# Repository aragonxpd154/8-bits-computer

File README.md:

<h1 align="center">

<br>
</h1>

<h4 align="center">

Computador de 8 bits feito só com lógica TTL (série 74LS), EEPROMs e temporizadores 555 —
**sem microcontrolador, sem CPU pronta**, "como antigamente". Projeto educacional e hobby,
com esquemas, placas (PCB) e manual para fabricar e montar tudo em casa.

</h4>

<p align="center">

</p>

<p align="center">

</p>

<p align="center">
<a href="#-o-que-é">O que é</a> ·
<a href="#-status">Status</a> ·
<a href="#-o-computador-montado">Montado</a> ·
<a href="#-as-placas-em-3d">Placas em 3D</a> ·
<a href="#-passo-a-passo-faça-você-mesmo">Faça você mesmo</a> ·
<a href="#-conteúdo-do-repositório">Conteúdo</a> ·
<a href="#-ferramentas">Ferramentas</a> ·
<a href="#-licença">Licença</a>
</p>

## 🧠 O que é

Um computador completo de 8 bits dividido em **13 módulos** (um deles opcional) + **1 backplane** (placa-mãe de interligação):

| Módulo | Principais CIs | Função |
|---|---|---|
| [Clock](docs/placas/clock-astavel-monoestavel.md) | NE556, 74LS00, 74LS04 | clock automático (0,7–140 Hz) ou passo a passo, HLT |
| [Reset](docs/placas/reset-circuito.md) | 74LS132 | reset por botão e ao ligar |
| [Contador de Programa](docs/placas/pc-contador-programa.md) | 74LS161, 74LS245 | endereço da próxima instrução |
| [RAM e MAR](docs/placas/ram-mar-memoria.md) | 2× 74S189, 74LS173, 4× 74LS157 | 16 bytes, programação manual por chaves DIP |
| [Registrador de Instrução](docs/placas/ir-registrador-instrucao.md) | 2× 74LS173, 74LS245 | opcode + operando |
| [Decodificador de Controle](docs/placas/cd-decodificador-controle.md) | 3× EEPROM 28C16 | microcódigo: 18 sinais de controle |
| [Palavra de Controle](docs/placas/cw-palavra-de-controle.md) *(opcional)* | 3× 74HCT541 | 18 LEDs: mostra os sinais de controle em cada passo |
| [Contador de Passos](docs/placas/fetch-contador-passos.md) | 74LS161, 74LS138 | passos T0…T4 |
| Registrador [A](docs/placas/acc-registrador-a.md) / [B](docs/placas/b-registrador-b.md) | 2× 74LS173 (+ 74LS245) | acumulador e segundo operando |
| [ULA](docs/placas/alu-unidade-logica-aritmetica.md) | 74LS283, 74LS86, 74LS08, 74LS32, 74LS153 | soma, subtração, AND, OR, XOR, NOT |
| [Registrador de Saída](docs/placas/out-registrador-saida.md) | 2× 74LS173 | valor do display |
| [Display Decimal](docs/placas/display-decimal.md) | 28C16, 555, 74LS161, 74LS139 | 0…255 ou −128…127 em 4 dígitos |
| [Backplane](docs/placas/backplane-barramento.md) |  | 5 V protegido, barramento D0…D7 com LEDs, todos os sinais |

**16 instruções:** `NOP LDA LDI STA ADD SUB AND OR XOR NOT JMP JC JZ OUT HLT` (JC/JZ prontos para uma futura placa de flags).
Detalhes em [docs/01-arquitetura.md](docs/01-arquitetura.md). Clique no nome de um módulo para ver a página dele.

## 🧱 O computador montado

As 14 placas numa base de madeira de 65 × 56 cm, em espaçadores de 25 mm, com tampa de acrílico. Os 58 cabos
passam por baixo das placas, presos com enforca-gatos. Na versão 3D os LEDs e o display funcionam de verdade:
a página roda o mesmo microcódigo das EEPROMs (Fibonacci, contador, tabuada…), com clock ajustável e passo a passo.

<p align="center"></p>

Arranjo, medidas e comprimento de cada cabo: [docs/05-interligacao-e-backplane.md](docs/05-interligacao-e-backplane.md).

## 🧊 As placas em 3D

Cada placa tem uma **página própria** explicando a função dela no computador, como o circuito funciona, o papel
de cada CI, o que cada LED mostra, o esquemático, a pinagem dos conectores, a lista de componentes e como testar —
além do **modelo 3D** (STL que o GitHub mostra girando no navegador, GLB com as cores reais e STEP para CAD).

<p align="center"></p>

➡️ **[Guia das 13 placas](docs/placas/README.md)** · 🧊 **[3D Viewer (GitHub Pages)](https://aragonxpd154.github.io/8-bits-computer/docs/3d/visualizador.html)** · [como usar e arquivos 3D](docs/3d/README.md)

<table>
<tr>
<td align="center" width="33%"><a href="docs/placas/ram-mar-memoria.md"><br><b>RAM e MAR</b></a></td>
<td align="center" width="33%"><a href="docs/placas/alu-unidade-logica-aritmetica.md"><br><b>ULA</b></a></td>
<td align="center" width="33%"><a href="docs/placas/display-decimal.md"><br><b>Display Decimal</b></a></td>
</tr>
<tr>
<td align="center"><a href="docs/placas/clock-astavel-monoestavel.md"><br><b>Clock</b></a></td>
<td align="center"><a href="docs/placas/cd-decodificador-controle.md"><br><b>Decodificador de Controle</b></a></td>
<td align="center"><a href="docs/placas/backplane-barramento.md"><br><b>Backplane</b></a></td>
</tr>
</table>

## 💻 Status

**Versão 3.0 (novembro/2026)**  projeto completo em **KiCad** (abre no Zorin OS/Ubuntu/Windows):

- [x] Esquemáticos de todos os módulos, com bloco de título e autoria
- [x] PCBs roteadas de todas as 14 placas, **DRC sem erros**  prontas para fabricação profissional (JLCPCB/PCBWay) e com **serigrafia didática** (sinais nos conectores e LEDs, valores dos componentes)
- [x] PDFs 1:1 para transferência térmica, fotolitos, mapa de furação e Gerbers para fabricação industrial
- [x] Backplane (antiga pasta *ASSEMBLY LAYOUT*, que estava vazia) e placa de Reset (que não tinha PCB)
- [x] Microcódigo completo (Python e C), EEPROM do display, montador e emulador
- [x] Teste automático do microcódigo: 14 programas de teste, um para cada instrução (`firmware/ferramentas/testar.py`)
- [x] Revisão de todos os circuitos  9 erros corrigidos (veja [docs/02-revisao-e-correcoes.md](docs/02-revisao-e-correcoes.md))
- [x] Manual completo de fabricação, montagem, gravação e uso
- [x] Página detalhada de cada placa, com diagrama de funcionamento e **modelo 3D** (STL, GLB, STEP e visualizador)
- [ ] Testes em bancada de cada placa produzida (o Clock da versão 2.1 já foi testado)
- [ ] Placa de flags (carry/zero) para `JC`/`JZ`

## ☕ Passo a passo (faça você mesmo)

> 🖼️ **Comece pelo [Guia visual passo a passo](docs/GUIA-VISUAL-PASSO-A-PASSO.md)**  todo o caminho em diagramas,
> do arquivo ao computador funcionando. Também em PDF:
> 📕 [Guia visual (PDF)](docs/pdf/guia-visual-passo-a-passo.pdf) · 📘 [Manual completo (PDF)](docs/pdf/manual-completo.pdf) ·
> 📄 [Esquema elétrico completo (PDF)](hardware/esquema-eletrico-completo.pdf)

Manual detalhado, capítulo por capítulo  tudo em português:

1. [Arquitetura](docs/01-arquitetura.md)  entenda o computador
2. [Revisão e correções](docs/02-revisao-e-correcoes.md)  o que mudou desde a versão EasyEDA
3. [Fabricação das placas](docs/03-fabricacao-das-placas.md)  enviar os Gerbers para a China (JLCPCB/PCBWay)
4. [Montagem das placas](docs/04-montagem-das-placas.md)  componente por componente, com testes
5. [Interligação e backplane](docs/05-interligacao-e-backplane.md)  os 58 cabos e o arranjo na base
6. [Gravação das EEPROMs](docs/06-gravacao-das-eeproms.md)  microcódigo e display com `minipro`
7. [Programação e uso](docs/07-programacao-e-uso.md)  escrever, montar e rodar programas
8. [Testes e diagnóstico](docs/08-testes-e-diagnostico.md)

📄 **Esquema elétrico completo em um único PDF:** [hardware/esquema-eletrico-completo.pdf](hardware/esquema-eletrico-completo.pdf)
🧾 **Lista de materiais:** [docs/lista-de-materiais-completa.md](docs/lista-de-materiais-completa.md)
🧊 **Cada placa explicada, em 3D:** [docs/placas/README.md](docs/placas/README.md)
🛠️ **Placas (imagens, tamanhos, arquivos):** [hardware/README.md](hardware/README.md)

## 📁 Conteúdo do repositório

```
8-bits-computer/
├── README.md                     este arquivo (visão geral, passo a passo, conteúdo)
├── CHANGELOG.md                  histórico de versões
├── LICENSE                       GPL-3.0
├── docs/                         MANUAL COMPLETO (pt-BR)
│   ├── GUIA-VISUAL-PASSO-A-PASSO.md  o projeto inteiro em diagramas, etapa por etapa
│   ├── placas/                       UMA PÁGINA POR PLACA: função, funcionamento, 3D, esquema, conectores, teste
│   ├── 3d/                           visualizador das placas, computador montado (montagem.html), modelos .glb/.stl
│   ├── pdf/                          guia visual e manual completo em PDF
│   ├── 01-arquitetura.md             blocos, instruções, tabela de todos os sinais
│   ├── 02-revisao-e-correcoes.md     erros corrigidos em relação à versão EasyEDA
│   ├── 03-fabricacao-das-placas.md   como pedir as PCBs no JLCPCB/PCBWay
│   ├── 04-montagem-das-placas.md     soldagem e teste de cada placa
│   ├── 05-interligacao-e-backplane.md os 58 cabos e o arranjo na base
│   ├── 06-gravacao-das-eeproms.md    gravação com minipro (Zorin/Ubuntu)
│   ├── 07-programacao-e-uso.md       painel, montador, emulador, exemplos
│   ├── 08-testes-e-diagnostico.md    subida do sistema e problemas comuns
│   ├── lista-de-materiais-completa.md
│   └── imagens/                      diagramas, imagens 2D/3D das placas, esquemas e diagramas de funcionamento
├── hardware/
│   ├── README.md                     tabela das 14 placas (tamanho, imagens, links)
│   ├── esquema-eletrico-completo.pdf capa + diagrama + interligação + 13 esquemáticos
│   ├── kicad/<placa>/                projeto KiCad (.kicad_pro / .kicad_sch / .kicad_pcb)
│   ├── kicad/bibliotecas/            símbolos e footprints do projeto
│   └── fabricacao/<placa>/           <placa>-gerber.zip (vai para a fábrica), esquemático PDF,
│                                     guia de montagem 1:1, mapa de furação, BOM, DRC, modelo 3D .step
├── firmware/
│   ├── microcodigo/                  EEPROM0/1/2.bin + gerador (Python e C)
│   ├── display/                      DISPLAY.bin + gerador
│   ├── programas/                    6 exemplos + 14 programas de teste (testes/)
│   └── ferramentas/                  montador.py, emulador.py e testar.py
└── tools/                            geradores: hardware (KiCad), 3D, documentação, diagramas, PDFs
```

### As 14 placas

| # | Placa (clique para a página) | Pasta |
|---|---|---|
| 1 | [Backplane / Barramento](docs/placas/backplane-barramento.md) | `backplane-barramento` |
| 2 | [Clock](docs/placas/clock-astavel-monoestavel.md) | `clock-astavel-monoestavel` |
| 3 | [Reset](docs/placas/reset-circuito.md) | `reset-circuito` |
| 4 | [Contador de Programa](docs/placas/pc-contador-programa.md) | `pc-contador-programa` |
| 5 | [RAM e MAR](docs/placas/ram-mar-memoria.md) | `ram-mar-memoria` |
| 6 | [Registrador de Instrução](docs/placas/ir-registrador-instrucao.md) | `ir-registrador-instrucao` |
| 7 | [Decodificador de Controle](docs/placas/cd-decodificador-controle.md) | `cd-decodificador-controle` |
| 8 | [Palavra de Controle](docs/placas/cw-palavra-de-controle.md) *(opcional)* | `cw-palavra-de-controle` |
| 9 | [Contador de Passos](docs/placas/fetch-contador-passos.md) | `fetch-contador-passos` |
| 10 | [Registrador A](docs/placas/acc-registrador-a.md) | `acc-registrador-a` |
| 11 | [Registrador B](docs/placas/b-registrador-b.md) | `b-registrador-b` |
| 12 | [ULA](docs/placas/alu-unidade-logica-aritmetica.md) | `alu-unidade-logica-aritmetica` |
| 13 | [Registrador de Saída](docs/placas/out-registrador-saida.md) | `out-registrador-saida` |
| 14 | [Display Decimal](docs/placas/display-decimal.md) | `display-decimal` |

> As versões antigas em EasyEDA (1.0V–3.0V, 2021) ficam preservadas no histórico do Git, na tag
> [`v2-easyeda`](https://github.com/aragonxpd154/8-bits-computer/tree/v2-easyeda).

## 🚀 Ferramentas

- [KiCad](https://www.kicad.org/) 7 ou superior  esquemáticos e PCBs
- [Freerouting](https://github.com/freerouting/freerouting)  autorroteamento
- [three.js](https://threejs.org/), trimesh e cascadio  modelos e visualizador 3D
- Python 3  microcódigo, montador, emulador e geradores
- `minipro` + TL866II Plus/T48  gravação das EEPROMs
- Histórico: EasyEDA, LTspice, MultisimLive, Hexplorer, Code::Blocks

Para regerar todo o hardware a partir da descrição em Python, veja [tools/gerador-kicad/README.md](tools/gerador-kicad/README.md).

## 📝 Licença

Este projeto está sob a licença GPL v3.0. Veja o arquivo [LICENSE](LICENSE).

---

Projeto e autoria: **Marcos Silva dos Santos (MarcosObel)** ♥  [LinkedIn](https://www.linkedin.com/in/marcosobel) · [GitHub](https://github.com/aragonxpd154)

<sub>English summary: an 8-bit TTL computer (SAP-1 style, no microcontroller) by Marcos Silva dos Santos. Version 3.0 contains complete KiCad schematics and home-fabrication-friendly PCBs for all 13 boards, corrected microcode, EEPROM images, an assembler/emulator, a page per board with 3D models (STL/GLB/STEP and an interactive viewer), and a full build manual (in Portuguese) under `docs/`.</sub>

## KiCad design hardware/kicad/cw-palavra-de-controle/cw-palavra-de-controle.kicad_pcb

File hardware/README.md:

# Hardware — Computador 8 Bits v3.0

> Projeto e PCBs de **Marcos Silva dos Santos** (MarcosObel) — GPL-3.0. Gerado por `tools/gerar_docs.py`.

- `kicad/<placa>/` — projeto KiCad (abra o `.kicad_pro`). Formato KiCad 7 (abre no 7, 8 e 9).
- `fabricacao/<placa>/` — **Gerber para a fábrica**, guia de montagem 1:1, esquemático, BOM, relatório DRC.
- [`esquema-eletrico-completo.pdf`](esquema-eletrico-completo.pdf) — todos os esquemáticos num único PDF.
- `fabricacao/<placa>/<placa>.step` — modelo 3D mecânico; modelos para visualizar em [`docs/3d/`](../docs/3d/README.md).
- **Explicação detalhada de cada placa:** [docs/placas](../docs/placas/README.md).

Todas: 2 camadas, furo metalizado, trilha 0,5 mm (alimentação 0,9 mm), isolação 0,4 mm, vias 1,6/0,8 mm, 4 furos M3 nos cantos, serigrafia didática. Como pedir: [docs/03-fabricacao-das-placas.md](../docs/03-fabricacao-das-placas.md).

| Placa | Tamanho (mm) | Vias | Trilhas na face de cima | Esquema | Fabricação |
|---|---|---:|---:|---|---|
| **Clock Astavel / Monoestavel** | 105 × 86 | 4 | 96 segmentos | [PDF](fabricacao/clock-astavel-monoestavel/0-esquematico.pdf) | [arquivos](fabricacao/clock-astavel-monoestavel/) |
| **Circuito de Reset** | 67 × 58 | 0 | 33 segmentos | [PDF](fabricacao/reset-circuito/0-esquematico.pdf) | [arquivos](fabricacao/reset-circuito/) |
| **Contador de Programa (PC)** | 92 × 69 | 5 | 93 segmentos | [PDF](fabricacao/pc-contador-programa/0-esquematico.pdf) | [arquivos](fabricacao/pc-contador-programa/) |
| **Memoria RAM e MAR** | 145 × 139 | 151 | 866 segmentos | [PDF](fabricacao/ram-mar-memoria/0-esquematico.pdf) | [arquivos](fabricacao/ram-mar-memoria/) |
| **Registrador de Instrucao (IR)** | 102 × 69 | 6 | 125 segmentos | [PDF](fabricacao/ir-registrador-instrucao/0-esquematico.pdf) | [arquivos](fabricacao/ir-registrador-instrucao/) |
| **Decodificador de Controle (microcodigo)** | 161 × 61 | 6 | 144 segmentos | [PDF](fabricacao/cd-decodificador-controle/0-esquematico.pdf) | [arquivos](fabricacao/cd-decodificador-controle/) |
| **Palavra de Controle (18 LEDs)** | 145 × 82 | 25 | 289 segmentos | [PDF](fabricacao/cw-palavra-de-controle/0-esquematico.pdf) | [arquivos](fabricacao/cw-palavra-de-controle/) |
| **Contador de Passos (Fetch/Execute)** | 70 × 69 | 2 | 86 segmentos | [PDF](fabricacao/fetch-contador-passos/0-esquematico.pdf) | [arquivos](fabricacao/fetch-contador-passos/) |
| **Registrador A (Acumulador)** | 110 × 69 | 4 | 174 segmentos | [PDF](fabricacao/acc-registrador-a/0-esquematico.pdf) | [arquivos](fabricacao/acc-registrador-a/) |
| **Registrador B** | 110 × 69 | 8 | 160 segmentos | [PDF](fabricacao/b-registrador-b/0-esquematico.pdf) | [arquivos](fabricacao/b-registrador-b/) |
| **Unidade Logica e Aritmetica (ULA)** | 218 × 128 | 145 | 837 segmentos | [PDF](fabricacao/alu-unidade-logica-aritmetica/0-esquematico.pdf) | [arquivos](fabricacao/alu-unidade-logica-aritmetica/) |
| **Registrador de Saida (OUT)** | 110 × 69 | 0 | 95 segmentos | [PDF](fabricacao/out-registrador-saida/0-esquematico.pdf) | [arquivos](fabricacao/out-registrador-saida/) |
| **Display Decimal** | 134 × 112 | 11 | 174 segmentos | [PDF](fabricacao/display-decimal/0-esquematico.pdf) | [arquivos](fabricacao/display-decimal/) |
| **Backplane / Barramento (Assembly Layout)** | 204 × 153 | 14 | 202 segmentos | [PDF](fabricacao/backplane-barramento/0-esquematico.pdf) | [arquivos](fabricacao/backplane-barramento/) |

Vermelho = cobre da face de cima (componentes) · azul = cobre da face de baixo (solda) · amarelo = serigrafia.

## Clock Astavel / Monoestavel

NE556: metade astavel (clock automatico ajustavel) e metade monoestavel (passo manual sem repique). Chave AUTO/MANUAL, entrada HLT.

🧊 **[Página completa da placa](../docs/placas/clock-astavel-monoestavel.md)** (função, funcionamento, esquema, conectores, teste) · [3D (STL)](../docs/3d/stl/clock-astavel-monoestavel.stl) · [STEP](fabricacao/clock-astavel-monoestavel/clock-astavel-monoestavel.step)

| Em 3D | Cobre e serigrafia |
|---|---|
|  |  |

## Circuito de Reset

Gera RST e ~{RST} (botao + reset automatico ao ligar) e o ~{STEPCLR} do contador de passos (= ~{RST} AND ~{Y5}).

🧊 **[Página completa da placa](../docs/placas/reset-circuito.md)** (função, funcionamento, esquema, conectores, teste) · [3D (STL)](../docs/3d/stl/reset-circuito.stl) · [STEP](fabricacao/reset-circuito/reset-circuito.step)

| Em 3D | Cobre e serigrafia |
|---|---|
|  |  |

## Contador de Programa (PC)

Contador de 4 bits (74LS161) com carga (JMP) e saida para o barramento (74LS245).

🧊 **[Página completa da placa](../docs/placas/pc-contador-programa.md)** (função, funcionamento, esquema, conectores, teste) · [3D (STL)](../docs/3d/stl/pc-contador-programa.stl) · [STEP](fabricacao/pc-contador-programa/pc-contador-programa.step)

| Em 3D | Cobre e serigrafia |
|---|---|
|  |  |

## Memoria RAM e MAR

MAR (74LS173), RAM 16x8 (2x 74S189), multiplexadores PROG/RUN (74LS157), gravacao manual por chaves DIP e pulso de escrita sincronizado ao clock.

🧊 **[Página completa da placa](../docs/placas/ram-mar-memoria.md)** (função, funcionamento, esquema, conectores, teste) · [3D (STL)](../docs/3d/stl/ram-mar-memoria.stl) · [STEP](fabricacao/ram-mar-memoria/ram-mar-memoria.step)

| Em 3D | Cobre e serigrafia |
|---|---|
|  |  |

## Registrador de Instrucao (IR)

Guarda a instrucao: nibble alto = opcode (para o decodificador), nibble baixo = operando (volta ao barramento por ~{IRO}).

🧊 **[Página completa da placa](../docs/placas/ir-registrador-instrucao.md)** (função, funcionamento, esquema, conectores, teste) · [3D (STL)](../docs/3d/stl/ir-registrador-instrucao.stl) · [STEP](fabricacao/ir-registrador-instrucao/ir-registrador-instrucao.step)

| Em 3D | Cobre e serigrafia |
|---|---|
|  |  |

## Decodificador de Controle (microcodigo)

3 EEPROMs 28C16 com o microcodigo: endereco = FLAGS(A8:A7) OPCODE(A6:A3) PASSO(A2:A0).

🧊 **[Página completa da placa](../docs/placas/cd-decodificador-controle.md)** (função, funcionamento, esquema, conectores, teste) · [3D (STL)](../docs/3d/stl/cd-decodificador-controle.stl) · [STEP](fabricacao/cd-decodificador-controle/cd-decodificador-controle.step)

| Em 3D | Cobre e serigrafia |
|---|---|
|  |  |

## Palavra de Controle (18 LEDs)

Fica entre o Decodificador de Controle e o backplane (que nao muda): recebe os 5 V do conector P_CD e repassa ao Decodificador por J12. 3x 74HCT541 repetem os 20 sinais das EEPROMs (reforcam a saida das EEPROMs) e 18 LEDs mostram cada sinal de controle: LED aceso = sinal ATIVO, inclusive nos sinais com barra (ativos em 0). Opcional: sem ela, os cabos do Decodificador vao direto ao backplane.

🧊 **[Página completa da placa](../docs/placas/cw-palavra-de-controle.md)** (função, funcionamento, esquema, conectores, teste) · [3D (STL)](../docs/3d/stl/cw-palavra-de-controle.stl) · [STEP](fabricacao/cw-palavra-de-controle/cw-palavra-de-controle.step)

| Em 3D | Cobre e serigrafia |
|---|---|
|  |  |

## Contador de Passos (Fetch/Execute)

Contador de passos T0..T4 (74LS161 + 74LS138). ~{Y5} reinicia o contador via placa de Reset.

🧊 **[Página completa da placa](../docs/placas/fetch-contador-passos.md)** (função, funcionamento, esquema, conectores, teste) · [3D (STL)](../docs/3d/stl/fetch-contador-passos.stl) · [STEP](fabricacao/fetch-contador-passos/fetch-contador-passos.step)

| Em 3D | Cobre e serigrafia |
|---|---|
|  |  |

## Registrador A (Acumulador)

Registrador A de 8 bits (2x 74LS173) com saida para o barramento (74LS245) e saida permanente para a ULA.

🧊 **[Página completa da placa](../docs/placas/acc-registrador-a.md)** (função, funcionamento, esquema, conectores, teste) · [3D (STL)](../docs/3d/stl/acc-registrador-a.stl) · [STEP](fabricacao/acc-registrador-a/acc-registrador-a.step)

| Em 3D | Cobre e serigrafia |
|---|---|
|  |  |

## Registrador B

Registrador B de 8 bits; alimenta a entrada B da ULA.

🧊 **[Página completa da placa](../docs/placas/b-registrador-b.md)** (função, funcionamento, esquema, conectores, teste) · [3D (STL)](../docs/3d/stl/b-registrador-b.stl) · [STEP](fabricacao/b-registrador-b/b-registrador-b.step)

| Em 3D | Cobre e serigrafia |
|---|---|
|  |  |

## Unidade Logica e Aritmetica (ULA)

Soma/subtracao (2x 74LS283 + 74LS86), AND, OR, XOR e NOT, selecionados por AL1:AL0 em 4x 74LS153.

🧊 **[Página completa da placa](../docs/placas/alu-unidade-logica-aritmetica.md)** (função, funcionamento, esquema, conectores, teste) · [3D (STL)](../docs/3d/stl/alu-unidade-logica-aritmetica.stl) · [STEP](fabricacao/alu-unidade-logica-aritmetica/alu-unidade-logica-aritmetica.step)

| Em 3D | Cobre e serigrafia |
|---|---|
|  |  |

## Registrador de Saida (OUT)

Registrador de saida: guarda o valor exibido pelo display decimal.

🧊 **[Página completa da placa](../docs/placas/out-registrador-saida.md)** (função, funcionamento, esquema, conectores, teste) · [3D (STL)](../docs/3d/stl/out-registrador-saida.stl) · [STEP](fabricacao/out-registrador-saida/out-registrador-saida.step)

| Em 3D | Cobre e serigrafia |
|---|---|
|  |  |

## Display Decimal

Converte o valor de 8 bits do registrador OUT em decimal (0..255 ou -128..127) por EEPROM 28C16 e varredura de 4 digitos (555 + 74LS161 + 74LS139).

🧊 **[Página completa da placa](../docs/placas/display-decimal.md)** (função, funcionamento, esquema, conectores, teste) · [3D (STL)](../docs/3d/stl/display-decimal.stl) · [STEP](fabricacao/display-decimal/display-decimal.step)

| Em 3D | Cobre e serigrafia |
|---|---|
|  |  |

## Backplane / Barramento (Assembly Layout)

Placa-mae de interligacao: entrada de 5 V protegida, distribuicao de alimentacao, barramento de dados D0..D7 com LEDs, e roteamento de todos os sinais de controle entre os modulos. Cada conector tem a mesma pinagem do conector correspondente no modulo: use cabos de 4 vias RETOS (pino 1 com pino 1).

🧊 **[Página completa da placa](../docs/placas/backplane-barramento.md)** (função, funcionamento, esquema, conectores, teste) · [3D (STL)](../docs/3d/stl/backplane-barramento.stl) · [STEP](fabricacao/backplane-barramento/backplane-barramento.step)

| Em 3D | Cobre e serigrafia |
|---|---|
|  |  |

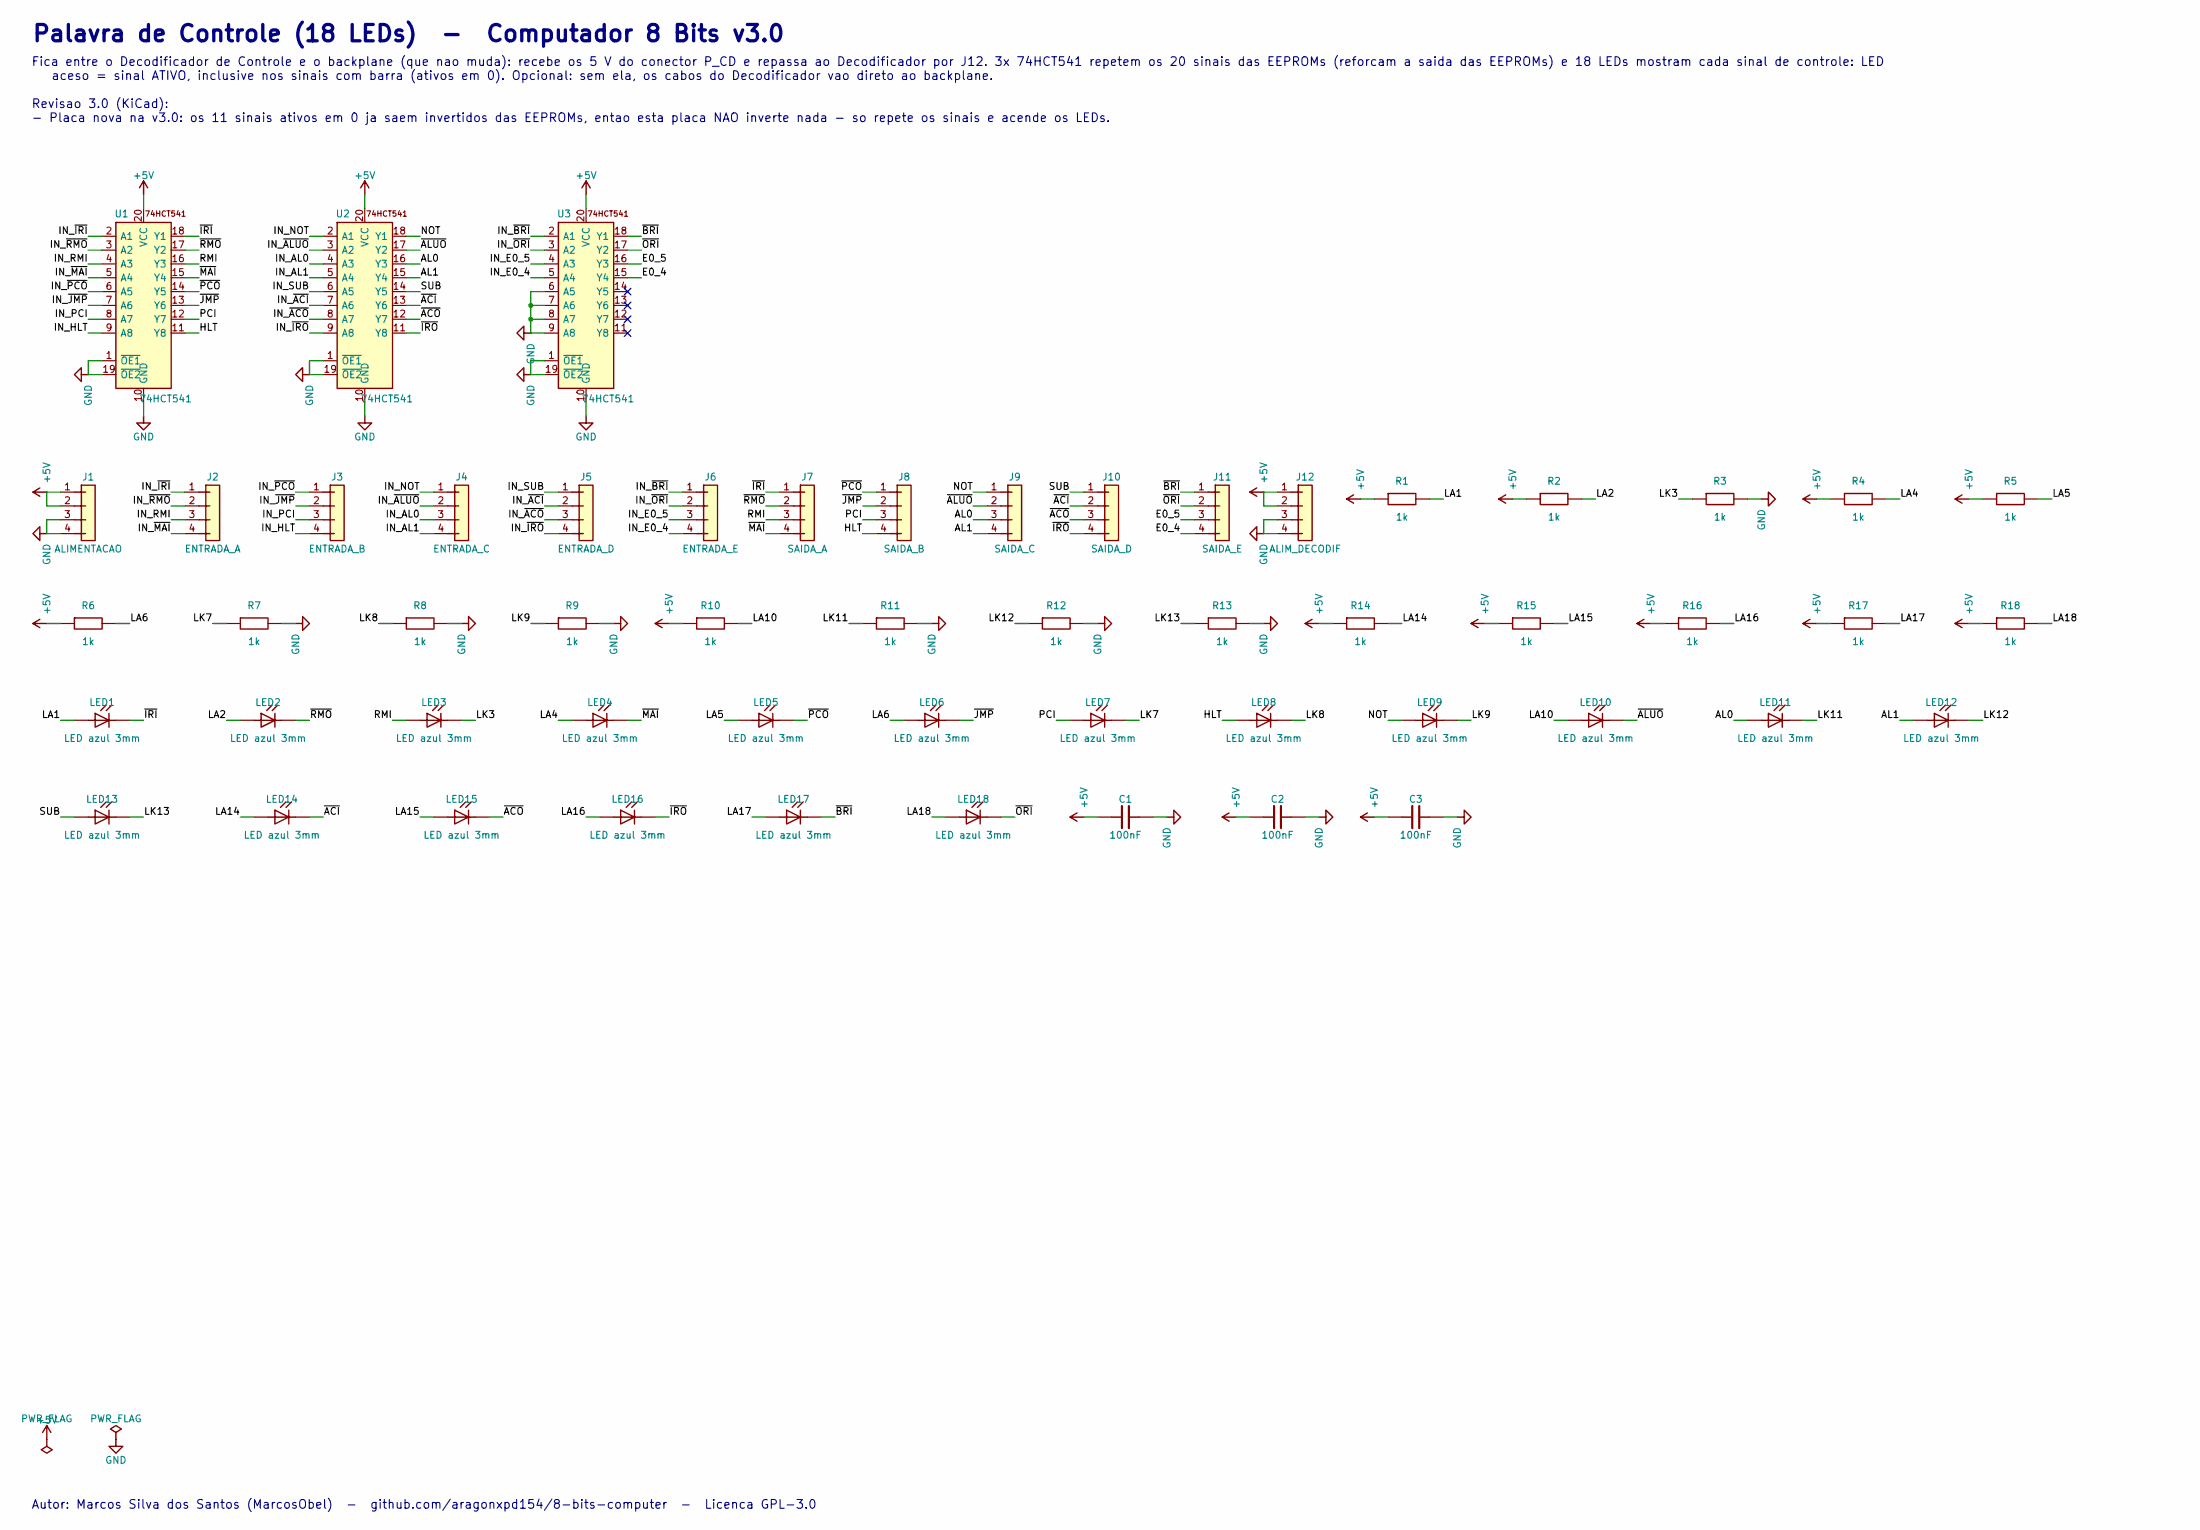
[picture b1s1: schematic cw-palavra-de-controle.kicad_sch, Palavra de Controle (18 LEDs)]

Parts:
C1, C2, C3: 100nF; C_Disc_D5.0mm_W2.5mm_P5.00mm
J1: ALIMENTACAO; PinHeader_1x04_P2.54mm_Vertical
J2: ENTRADA_A; PinHeader_1x04_P2.54mm_Vertical
J3: ENTRADA_B; PinHeader_1x04_P2.54mm_Vertical
J4: ENTRADA_C; PinHeader_1x04_P2.54mm_Vertical
J5: ENTRADA_D; PinHeader_1x04_P2.54mm_Vertical
J6: ENTRADA_E; PinHeader_1x04_P2.54mm_Vertical
J7: SAIDA_A; PinHeader_1x04_P2.54mm_Vertical
J8: SAIDA_B; PinHeader_1x04_P2.54mm_Vertical
J9: SAIDA_C; PinHeader_1x04_P2.54mm_Vertical
J10: SAIDA_D; PinHeader_1x04_P2.54mm_Vertical
J11: SAIDA_E; PinHeader_1x04_P2.54mm_Vertical
J12: ALIM_DECODIF; PinHeader_1x04_P2.54mm_Vertical
LED1, LED2, LED3, LED4, LED5, LED6, LED7, LED8, LED9, LED10, LED11, LED12, LED13, LED14, LED15, LED16, LED17, LED18: LED azul 3mm; LED_D3.0mm
R1, R2, R3, R4, R5, R6, R7, R8, R9, R10, R11, R12, R13, R14, R15, R16, R17, R18: 1k; R_Axial_DIN0207_L6.3mm_D2.5mm_P10.16mm_Horizontal
U1, U2, U3: 74HCT541; DIP-20_W7.62mm_LongPads

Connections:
+5V: C1.1, C2.1, C3.1, J1.1, J1.2, J12.1, J12.2, R1.1, R2.1, R4.1, R5.1, R6.1, R10.1, R14.1, R15.1, R16.1, R17.1, R18.1, U1.20 (VCC), U2.20 (VCC), U3.20 (VCC)
AL0: J9.3, LED11.2 (A), U2.16 (Y3)
AL1: J9.4, LED12.2 (A), U2.15 (Y4)
E0_4: J11.4, U3.15 (Y4)
E0_5: J11.3, U3.16 (Y3)
GND: C1.2, C2.2, C3.2, J1.3, J1.4, J12.3, J12.4, R3.2, R7.2, R8.2, R9.2, R11.2, R12.2, R13.2, U1.1 (~OE1), U1.10 (GND), U1.19 (~OE2), U2.1 (~OE1), U2.10 (GND), U2.19 (~OE2), U3.1 (~OE1), U3.6 (A5), U3.7 (A6), U3.8 (A7), U3.9 (A8), U3.10 (GND), U3.19 (~OE2)
HLT: J8.4, LED8.2 (A), U1.11 (Y8)
IN_AL0: J4.3, U2.4 (A3)
IN_AL1: J4.4, U2.5 (A4)
IN_E0_4: J6.4, U3.5 (A4)
IN_E0_5: J6.3, U3.4 (A3)
IN_HLT: J3.4, U1.9 (A8)
IN_NOT: J4.1, U2.2 (A1)
IN_PCI: J3.3, U1.8 (A7)
IN_RMI: J2.3, U1.4 (A3)
IN_SUB: J5.1, U2.6 (A5)
IN_~ACI: J5.2, U2.7 (A6)
IN_~ACO: J5.3, U2.8 (A7)
IN_~ALUO: J4.2, U2.3 (A2)
IN_~BRI: J6.1, U3.2 (A1)
IN_~IRI: J2.1, U1.2 (A1)
IN_~IRO: J5.4, U2.9 (A8)
IN_~JMP: J3.2, U1.7 (A6)
IN_~MAI: J2.4, U1.5 (A4)
IN_~ORI: J6.2, U3.3 (A2)
IN_~PCO: J3.1, U1.6 (A5)
IN_~RMO: J2.2, U1.3 (A2)
LA1: LED1.2 (A), R1.2
LA2: LED2.2 (A), R2.2
LA4: LED4.2 (A), R4.2
LA5: LED5.2 (A), R5.2
LA6: LED6.2 (A), R6.2
LA10: LED10.2 (A), R10.2
LA14: LED14.2 (A), R14.2
LA15: LED15.2 (A), R15.2
LA16: LED16.2 (A), R16.2
LA17: LED17.2 (A), R17.2
LA18: LED18.2 (A), R18.2
LK3: LED3.1 (K), R3.1
LK7: LED7.1 (K), R7.1
LK8: LED8.1 (K), R8.1
LK9: LED9.1 (K), R9.1
LK11: LED11.1 (K), R11.1
LK12: LED12.1 (K), R12.1
LK13: LED13.1 (K), R13.1
NOT: J9.1, LED9.2 (A), U2.18 (Y1)
PCI: J8.3, LED7.2 (A), U1.12 (Y7)
RMI: J7.3, LED3.2 (A), U1.16 (Y3)
SUB: J10.1, LED13.2 (A), U2.14 (Y5)
~ACI: J10.2, LED14.1 (K), U2.13 (Y6)
~ACO: J10.3, LED15.1 (K), U2.12 (Y7)
~ALUO: J9.2, LED10.1 (K), U2.17 (Y2)
~BRI: J11.1, LED17.1 (K), U3.18 (Y1)
~IRI: J7.1, LED1.1 (K), U1.18 (Y1)
~IRO: J10.4, LED16.1 (K), U2.11 (Y8)
~JMP: J8.2, LED6.1 (K), U1.13 (Y6)
~MAI: J7.4, LED4.1 (K), U1.15 (Y4)
~ORI: J11.2, LED18.1 (K), U3.17 (Y2)
~PCO: J8.1, LED5.1 (K), U1.14 (Y5)
~RMO: J7.2, LED2.1 (K), U1.17 (Y2)

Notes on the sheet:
Palavra de Controle (18 LEDs) - Computador 8 Bits v3.0
Fica entre o Decodificador de Controle e o backplane (que nao muda): recebe os 5 V do conector P_CD e repassa ao Decodificador por J12. 3x 74HCT541 repetem os 20 sinais das EEPROMs (reforcam a saida das EEPROMs) e 18 LEDs mostram cada sinal de controle: LED aceso = sinal ATIVO, inclusive nos sinais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
Autor: Marcos Silva dos Santos (MarcosObel) - github.com/aragonxpd154/8-bits-computer - Licenca GPL-3.0

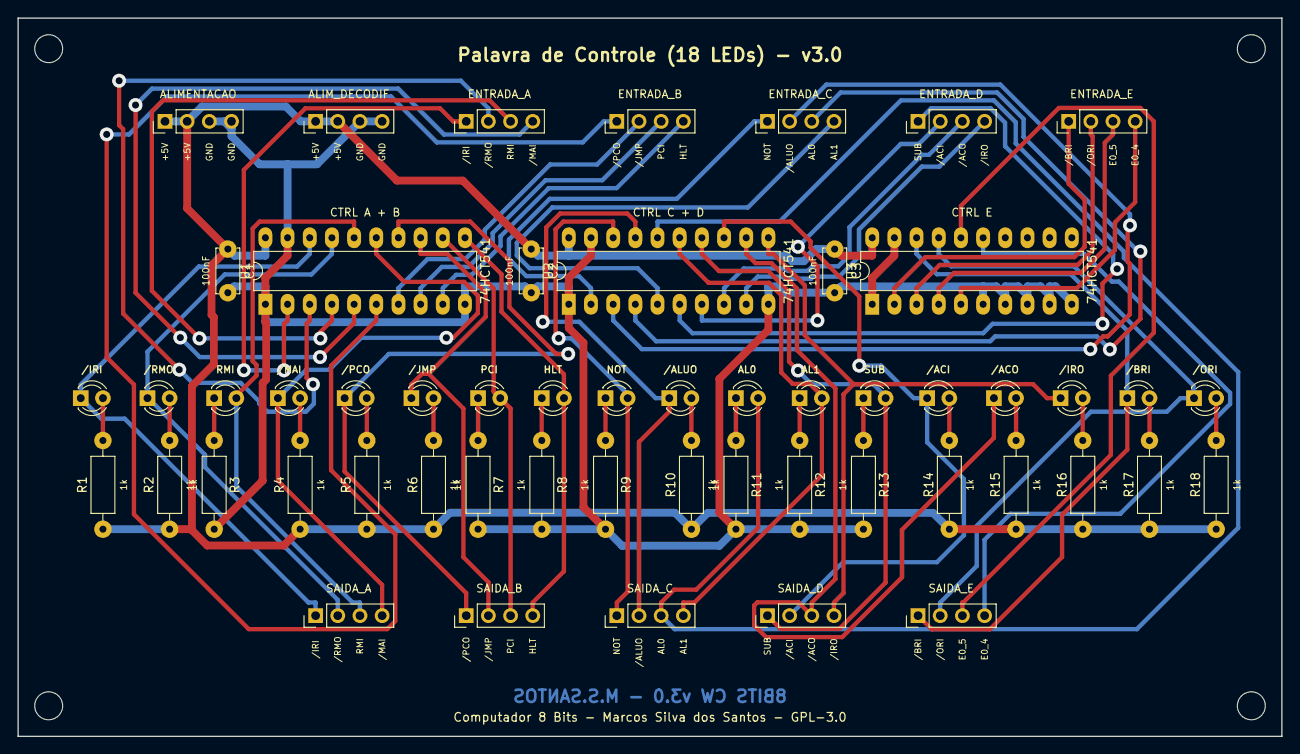
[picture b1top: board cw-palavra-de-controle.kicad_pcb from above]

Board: 2 copper layers, 144.7 x 82.3 mm, 58 parts (0 on the bottom side), 60 nets.

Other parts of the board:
H1, H2, H3, H4: MountingHole_3.2mm_M3

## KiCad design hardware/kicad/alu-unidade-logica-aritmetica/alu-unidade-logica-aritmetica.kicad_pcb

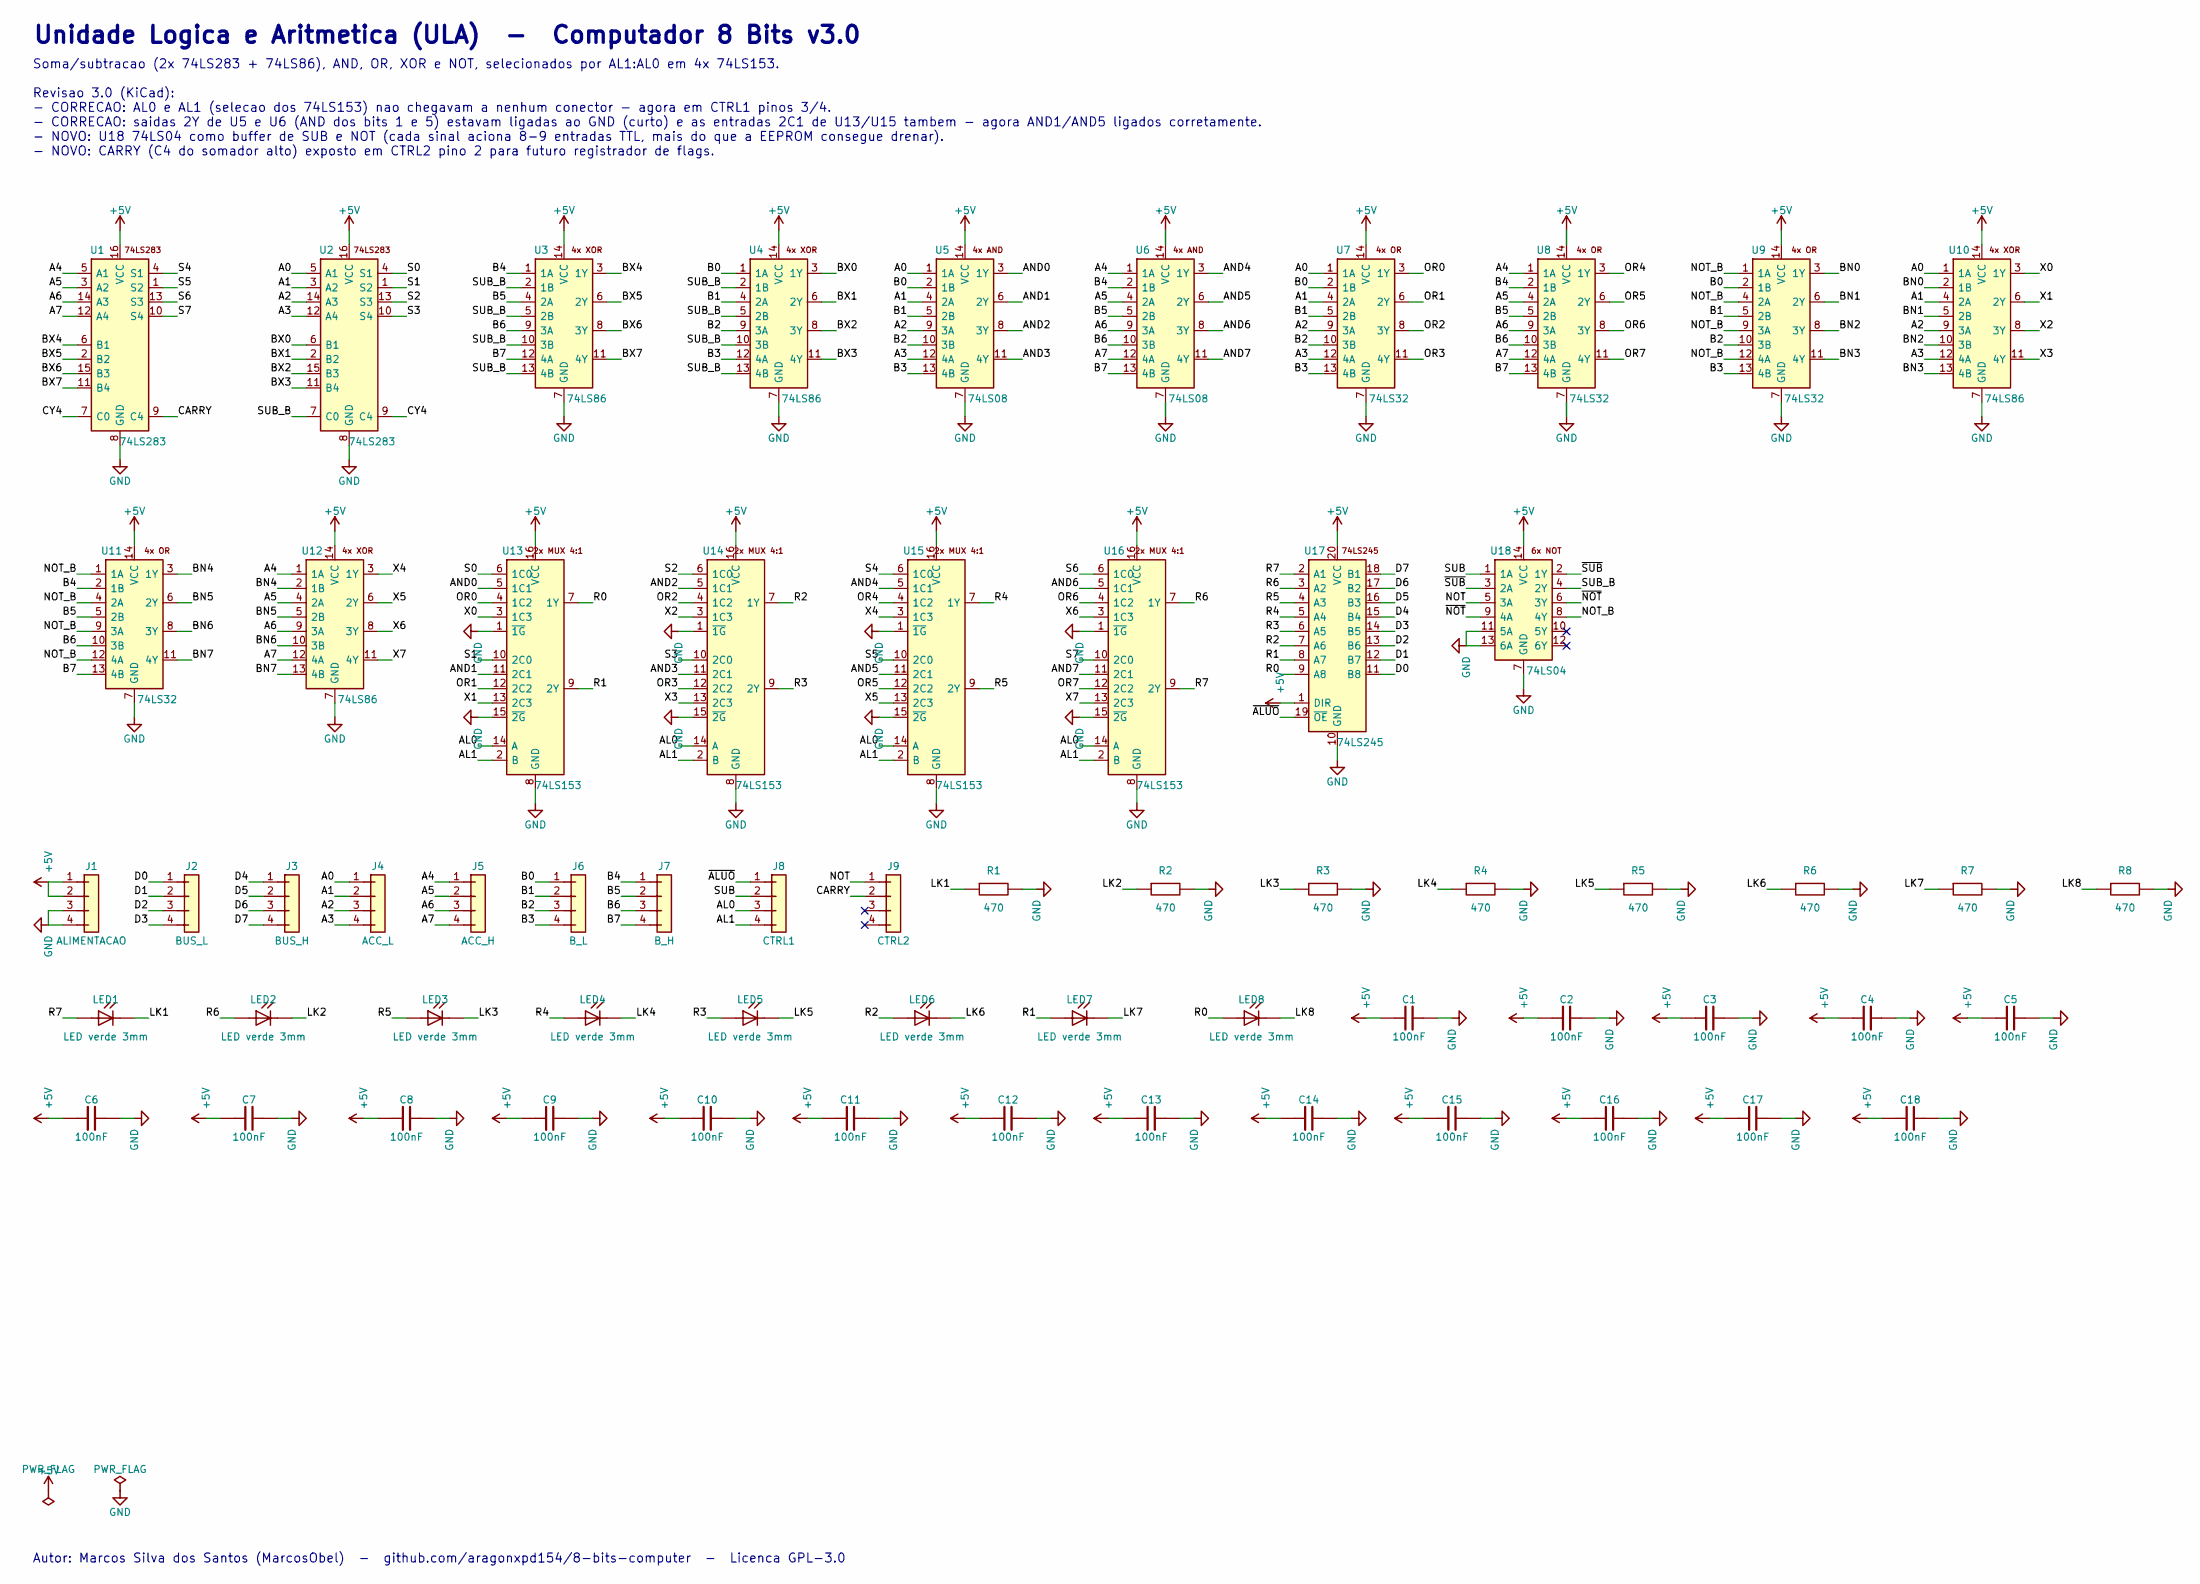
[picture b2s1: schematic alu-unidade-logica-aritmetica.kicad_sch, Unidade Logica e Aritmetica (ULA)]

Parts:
C1, C2, C3, C4, C5, C6, C7, C8, C9, C10, C11, C12, C13, C14, C15, C16, C17, C18: 100nF; C_Disc_D5.0mm_W2.5mm_P5.00mm
J1: ALIMENTACAO; PinHeader_1x04_P2.54mm_Vertical
J2: BUS_L; PinHeader_1x04_P2.54mm_Vertical
J3: BUS_H; PinHeader_1x04_P2.54mm_Vertical
J4: ACC_L; PinHeader_1x04_P2.54mm_Vertical
J5: ACC_H; PinHeader_1x04_P2.54mm_Vertical
J6: B_L; PinHeader_1x04_P2.54mm_Vertical
J7: B_H; PinHeader_1x04_P2.54mm_Vertical
J8: CTRL1; PinHeader_1x04_P2.54mm_Vertical
J9: CTRL2; PinHeader_1x04_P2.54mm_Vertical
LED1, LED2, LED3, LED4, LED5, LED6, LED7, LED8: LED verde 3mm; LED_D3.0mm
R1, R2, R3, R4, R5, R6, R7, R8: 470; R_Axial_DIN0207_L6.3mm_D2.5mm_P10.16mm_Horizontal
U1, U2: 74LS283; DIP-16_W7.62mm_LongPads
U3, U4, U10, U12: 74LS86; DIP-14_W7.62mm_LongPads
U5, U6: 74LS08; DIP-14_W7.62mm_LongPads
U7, U8, U9, U11: 74LS32; DIP-14_W7.62mm_LongPads
U13, U14, U15, U16: 74LS153; DIP-16_W7.62mm_LongPads
U17: 74LS245; DIP-20_W7.62mm_LongPads
U18: 74LS04; DIP-14_W7.62mm_LongPads

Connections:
+5V: C1.1, C2.1, C3.1, C4.1, C5.1, C6.1, C7.1, C8.1, C9.1, C10.1, C11.1, C12.1, C13.1, C14.1, C15.1, C16.1, C17.1, C18.1, J1.1, J1.2, U1.16 (VCC), U2.16 (VCC), U3.14 (VCC), U4.14 (VCC), U5.14 (VCC), U6.14 (VCC), U7.14 (VCC), U8.14 (VCC), U9.14 (VCC), U10.14 (VCC), U11.14 (VCC), U12.14 (VCC), U13.16 (VCC), U14.16 (VCC), U15.16 (VCC), U16.16 (VCC), U17.1 (DIR), U17.20 (VCC), U18.14 (VCC)
A0: J4.1, U2.5 (A1), U5.1 (1A), U7.1 (1A), U10.1 (1A)
A1: J4.2, U2.3 (A2), U5.4 (2A), U7.4 (2A), U10.4 (2A)
A2: J4.3, U2.14 (A3), U5.9 (3A), U7.9 (3A), U10.9 (3A)
A3: J4.4, U2.12 (A4), U5.12 (4A), U7.12 (4A), U10.12 (4A)
A4: J5.1, U1.5 (A1), U6.1 (1A), U8.1 (1A), U12.1 (1A)
A5: J5.2, U1.3 (A2), U6.4 (2A), U8.4 (2A), U12.4 (2A)
A6: J5.3, U1.14 (A3), U6.9 (3A), U8.9 (3A), U12.9 (3A)
A7: J5.4, U1.12 (A4), U6.12 (4A), U8.12 (4A), U12.12 (4A)
AL0: J8.3, U13.14 (A), U14.14 (A), U15.14 (A), U16.14 (A)
AL1: J8.4, U13.2 (B), U14.2 (B), U15.2 (B), U16.2 (B)
AND0: U5.3 (1Y), U13.5 (1C1)
AND1: U5.6 (2Y), U13.11 (2C1)
AND2: U5.8 (3Y), U14.5 (1C1)
AND3: U5.11 (4Y), U14.11 (2C1)
AND4: U6.3 (1Y), U15.5 (1C1)
AND5: U6.6 (2Y), U15.11 (2C1)
AND6: U6.8 (3Y), U16.5 (1C1)
AND7: U6.11 (4Y), U16.11 (2C1)
B0: J6.1, U4.1 (1A), U5.2 (1B), U7.2 (1B), U9.2 (1B)
B1: J6.2, U4.4 (2A), U5.5 (2B), U7.5 (2B), U9.5 (2B)
B2: J6.3, U4.9 (3A), U5.10 (3B), U7.10 (3B), U9.10 (3B)
B3: J6.4, U4.12 (4A), U5.13 (4B), U7.13 (4B), U9.13 (4B)
B4: J7.1, U3.1 (1A), U6.2 (1B), U8.2 (1B), U11.2 (1B)
B5: J7.2, U3.4 (2A), U6.5 (2B), U8.5 (2B), U11.5 (2B)
B6: J7.3, U3.9 (3A), U6.10 (3B), U8.10 (3B), U11.10 (3B)
B7: J7.4, U3.12 (4A), U6.13 (4B), U8.13 (4B), U11.13 (4B)
BN0: U9.3 (1Y), U10.2 (1B)
BN1: U9.6 (2Y), U10.5 (2B)
BN2: U9.8 (3Y), U10.10 (3B)
BN3: U9.11 (4Y), U10.13 (4B)
BN4: U11.3 (1Y), U12.2 (1B)
BN5: U11.6 (2Y), U12.5 (2B)
BN6: U11.8 (3Y), U12.10 (3B)
BN7: U11.11 (4Y), U12.13 (4B)
BX0: U2.6 (B1), U4.3 (1Y)
BX1: U2.2 (B2), U4.6 (2Y)
BX2: U2.15 (B3), U4.8 (3Y)
BX3: U2.11 (B4), U4.11 (4Y)
BX4: U1.6 (B1), U3.3 (1Y)
BX5: U1.2 (B2), U3.6 (2Y)
BX6: U1.15 (B3), U3.8 (3Y)
BX7: U1.11 (B4), U3.11 (4Y)
CARRY: J9.2, U1.9 (C4)
CY4: U1.7 (C0), U2.9 (C4)
D0: J2.1, U17.11 (B8)
D1: J2.2, U17.12 (B7)
D2: J2.3, U17.13 (B6)
D3: J2.4, U17.14 (B5)
D4: J3.1, U17.15 (B4)
D5: J3.2, U17.16 (B3)
D6: J3.3, U17.17 (B2)
D7: J3.4, U17.18 (B1)
GND: C1.2, C2.2, C3.2, C4.2, C5.2, C6.2, C7.2, C8.2, C9.2, C10.2, C11.2, C12.2, C13.2, C14.2, C15.2, C16.2, C17.2, C18.2, J1.3, J1.4, R1.2, R2.2, R3.2, R4.2, R5.2, R6.2, R7.2, R8.2, U1.8 (GND), U2.8 (GND), U3.7 (GND), U4.7 (GND), U5.7 (GND), U6.7 (GND), U7.7 (GND), U8.7 (GND), U9.7 (GND), U10.7 (GND), U11.7 (GND), U12.7 (GND), U13.1 (~1G), U13.8 (GND), U13.15 (~2G), U14.1 (~1G), U14.8 (GND), U14.15 (~2G), U15.1 (~1G), U15.8 (GND), U15.15 (~2G), U16.1 (~1G), U16.8 (GND), U16.15 (~2G), U17.10 (GND), U18.7 (GND), U18.11 (5A), U18.13 (6A)
LK1: LED1.1 (K), R1.1
LK2: LED2.1 (K), R2.1
LK3: LED3.1 (K), R3.1
LK4: LED4.1 (K), R4.1
LK5: LED5.1 (K), R5.1
LK6: LED6.1 (K), R6.1
LK7: LED7.1 (K), R7.1
LK8: LED8.1 (K), R8.1
NOT: J9.1, U18.5 (3A)
NOT_B: U9.1 (1A), U9.4 (2A), U9.9 (3A), U9.12 (4A), U11.1 (1A), U11.4 (2A), U11.9 (3A), U11.12 (4A), U18.8 (4Y)
OR0: U7.3 (1Y), U13.4 (1C2)
OR1: U7.6 (2Y), U13.12 (2C2)
OR2: U7.8 (3Y), U14.4 (1C2)
OR3: U7.11 (4Y), U14.12 (2C2)
OR4: U8.3 (1Y), U15.4 (1C2)
OR5: U8.6 (2Y), U15.12 (2C2)
OR6: U8.8 (3Y), U16.4 (1C2)
OR7: U8.11 (4Y), U16.12 (2C2)
R0: LED8.2 (A), U13.7 (1Y), U17.9 (A8)
R1: LED7.2 (A), U13.9 (2Y), U17.8 (A7)
R2: LED6.2 (A), U14.7 (1Y), U17.7 (A6)
R3: LED5.2 (A), U14.9 (2Y), U17.6 (A5)
R4: LED4.2 (A), U15.7 (1Y), U17.5 (A4)
R5: LED3.2 (A), U15.9 (2Y), U17.4 (A3)
R6: LED2.2 (A), U16.7 (1Y), U17.3 (A2)
R7: LED1.2 (A), U16.9 (2Y), U17.2 (A1)
S0: U2.4 (S1), U13.6 (1C0)
S1: U2.1 (S2), U13.10 (2C0)
S2: U2.13 (S3), U14.6 (1C0)
S3: U2.10 (S4), U14.10 (2C0)
S4: U1.4 (S1), U15.6 (1C0)
S5: U1.1 (S2), U15.10 (2C0)
S6: U1.13 (S3), U16.6 (1C0)
S7: U1.10 (S4), U16.10 (2C0)
SUB: J8.2, U18.1 (1A)
SUB_B: U2.7 (C0), U3.2 (1B), U3.5 (2B), U3.10 (3B), U3.13 (4B), U4.2 (1B), U4.5 (2B), U4.10 (3B), U4.13 (4B), U18.4 (2Y)
X0: U10.3 (1Y), U13.3 (1C3)
X1: U10.6 (2Y), U13.13 (2C3)
X2: U10.8 (3Y), U14.3 (1C3)
X3: U10.11 (4Y), U14.13 (2C3)
X4: U12.3 (1Y), U15.3 (1C3)
X5: U12.6 (2Y), U15.13 (2C3)
X6: U12.8 (3Y), U16.3 (1C3)
X7: U12.11 (4Y), U16.13 (2C3)
~ALUO: J8.1, U17.19 (~OE)
~NOT: U18.6 (3Y), U18.9 (4A)
~SUB: U18.2 (1Y), U18.3 (2A)

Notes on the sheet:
Unidade Logica e Aritmetica (ULA) - Computador 8 Bits v3.0
Soma/subtracao (2x 74LS283 + 74LS86), AND, OR, XOR e NOT, selecionados por AL1:AL0 em 4x 74LS153. Revisao 3.0 (KiCad): - CORRECAO: AL0 e AL1 (selecao dos 74LS153) nao chegavam a nenhum conector - agora em CTRL1 pinos 3/4. - CORRECAO: saidas 2Y de U5 e U6 (AND dos bits 1 e 5) estavam ligadas ao GND 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
Autor: Marcos Silva dos Santos (MarcosObel) - github.com/aragonxpd154/8-bits-computer - Licenca GPL-3.0

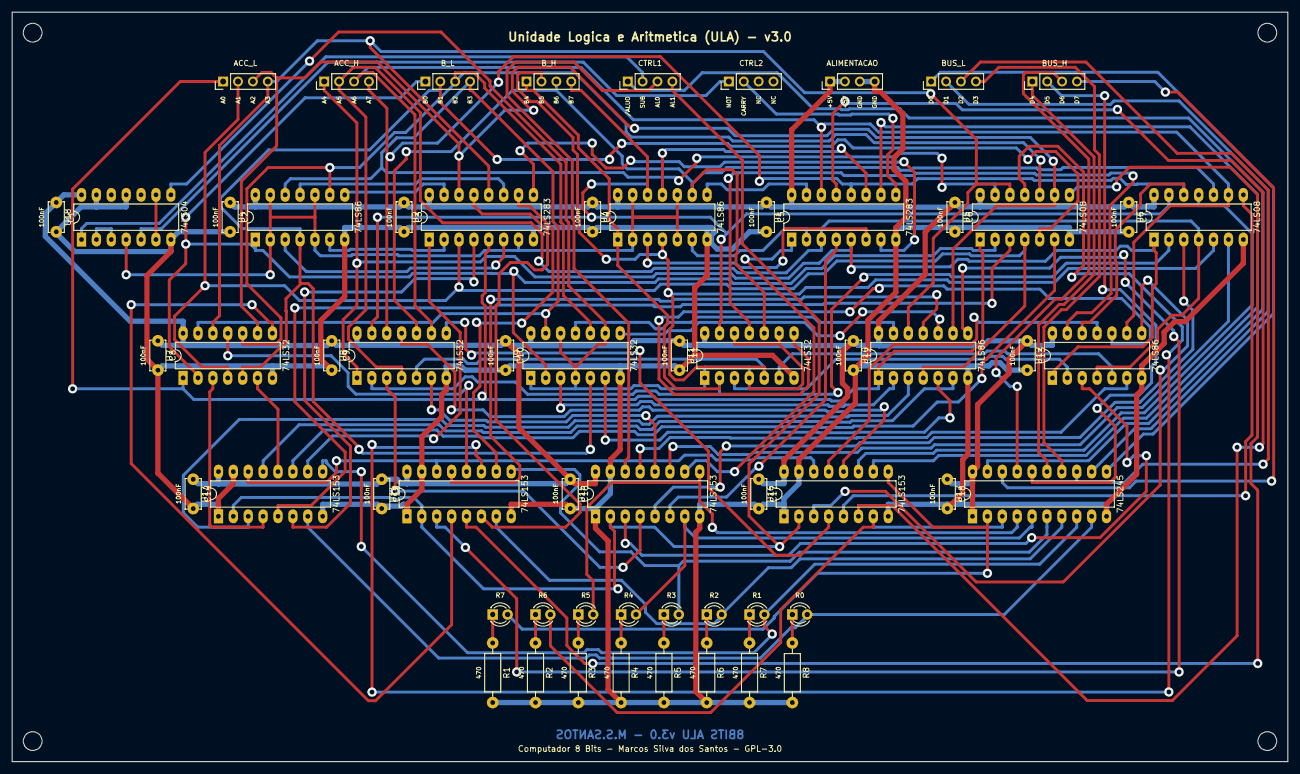
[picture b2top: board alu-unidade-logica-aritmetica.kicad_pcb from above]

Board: 2 copper layers, 217.5 x 127.8 mm, 65 parts (0 on the bottom side), 101 nets.

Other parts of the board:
H1, H2, H3, H4: MountingHole_3.2mm_M3

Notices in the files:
hardware/kicad/alu-unidade-logica-aritmetica/alu-unidade-logica-aritmetica.kicad_pcb:
github.com/aragonxpd154/8-bits-computer - GPL-3.0
Computador 8 Bits - Marcos Silva dos Santos - GPL-3.0
hardware/kicad/alu-unidade-logica-aritmetica/alu-unidade-logica-aritmetica.kicad_sch:
Licenca GPL-3.0 - Computador 8 Bits sem microcontrolador
